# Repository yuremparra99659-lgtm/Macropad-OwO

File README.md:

# Yuyo´s Utility Pad
Yuyo´s Utility Pad is a 6 key macropad that i designed in my free time as a way to learn new things

## Components
- 6 keys support
- a hidden led inside the case :)
- stickers (that i´ll add on the future)

## Files
On the folders you can find all the files that are used in this project but here is an overview so you can understand my view of it:

- Case:
  It is a simple case, the bottom is where the pcb is stored, the top just has the holes for the keycaps. The usb c port comes out thanks to a cut on the back of the case.
  I wanted to keep it simple so i could put stickers on it (i can´t decide between cat or alien)}

-PCB:
  The switches are arranged in a way that i like to call "wasd without the s", i couldn´t decide between a more conventional way and this one, but i think that it could be more useful      this way (it could be very nice for rythm games). On the center is the XIAO RP2040 and a LED that i hope it can be seen between the switch spaces.

-Code:
  I wanted to use Circuitpython mainly because i want to learn more about python in general, it´s something that i want to do but i never find a real motivation to do it, and this is a     good one.

## Materials
 - 6x Cherry MX Switches.
 - 6x Keycaps.
 - 4X M3x12mm SHCS Bolts.
 - 6x 1N4148 DO-35 Diodes.
 - 1x WS2812B LED
 - 1x XIAO RP2040
 - 1x Case (2 printed parts)

## Extra
This project was very fun to do, i fell in love with fusion 360 and kicad was really fun to use. I don´t remember when was the las time that i was so excited with a project so this was so awesome :).

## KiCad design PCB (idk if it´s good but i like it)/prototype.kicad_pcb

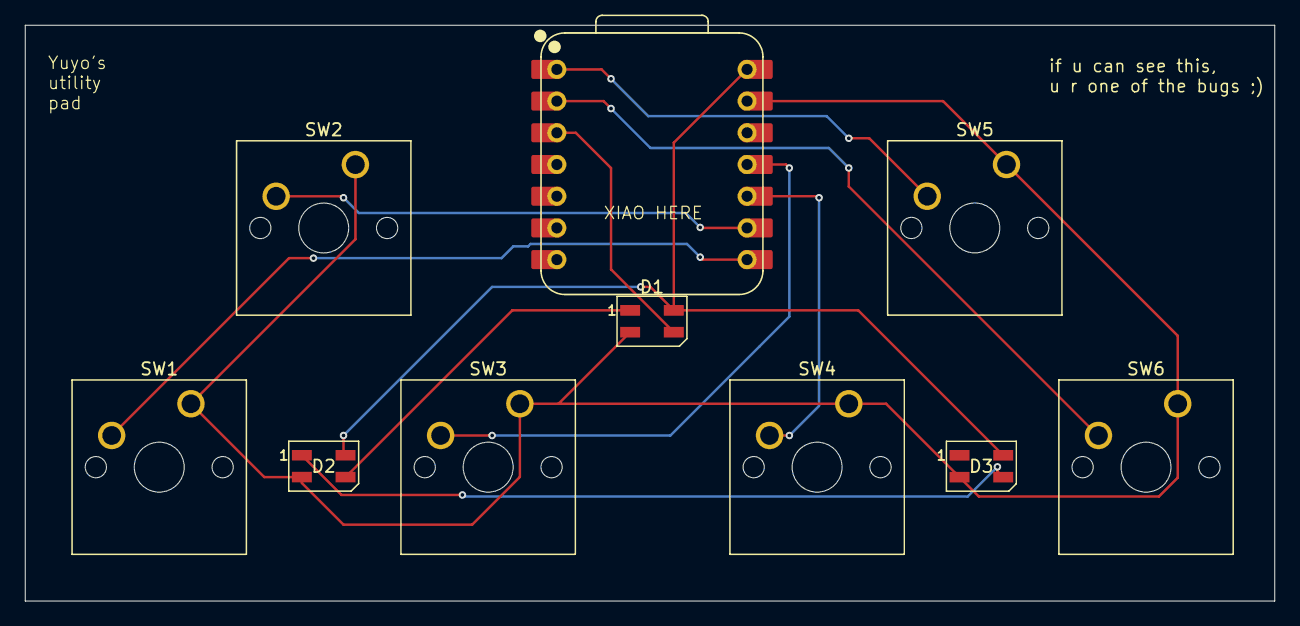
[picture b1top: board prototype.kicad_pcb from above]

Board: 2 copper layers, 100.1 x 46.1 mm, 10 parts (0 on the bottom side), 11 nets.

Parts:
D1, D2, D3: SK6812MINI; LED_SK6812MINI_PLCC4_3.5x3.5mm_P1.75mm
SW1, SW2, SW3, SW4, SW5, SW6: SW_Push; SW_Cherry_MX_1.00u_PCB
U1: XIAO-RP2040-DIP

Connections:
+5V: D1.4 (VDD), D2.4 (VDD), D3.4 (VDD), U1.14 (VBUS)
GND: D1.2 (VSS), D2.2 (VSS), D3.2 (VSS), SW1.1, SW2.1, SW3.1, SW4.1, SW5.1, SW6.1, U1.13 (GND)
unnamed: D1.3 (DIN), U1.3 (GPIO28/ADC2/A2)
unnamed: D1.1 (DOUT), D2.3 (DIN)
unnamed: D2.1 (DOUT), D3.3 (DIN)
unnamed: SW1.2, U1.8 (GPIO1/RX)
unnamed: SW2.2, U1.9 (GPIO2/SCK)
unnamed: SW3.2, U1.11 (GPIO3/MOSI)
unnamed: SW4.2, U1.10 (GPIO4/MISO)
unnamed: SW5.2, U1.1 (GPIO26/ADC0/A0)
unnamed: SW6.2, U1.2 (GPIO27/ADC1/A1)
